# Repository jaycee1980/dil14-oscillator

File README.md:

# dil14-oscillator
A DIL-16 oscillator using a 3.2x2.5mm SMD crystal. Originally I made this for Commodore Amigas, because the 28.6363MHz and 28.37516MHz oscillators are becoming hard to get. Most modern oscillators now are 3.3V types

I found that while they're not common, it IS possible to get crystals of those frequencies in SMD format. For example Mouser have [CTS 403C35D28M37500](https://www.mouser.co.uk/ProductDetail/CTS-Electronic-Components/403C35D28M37500?qs=tjlMjqRIEYSI3TNJCnGYSw%3D%3D) and [ECS 520-286.3-18-33-JGNT](https://www.mouser.co.uk/ProductDetail/ECS/ECS-286.3-18-33-JGN-TR?qs=wd5RIQLrsJjqi%252B%2F66hueEA%3D%3D). These are suitable for use with an Amiga, but they need an oscillator circuit to work. This was easily achievable with the usual Pierce oscillator configuration using logic gates. 

I chose to use a "picogate" type part to keep the size small, the 74LVC2GU04. This is a SOT23-6 part (aka SOT457 o TSOP6) and perfect for the job. 

I've also found that LCSC have suitable crystals in their inventory. They are:

https://www.lcsc.com/product-detail/Crystals_TXC-Corp-7V-28-63636MAHJ-T_C2595058.html

https://www.lcsc.com/product-detail/Crystals_YXC-Crystal-Oscillators-X322528375MSB4SI_C20618000.html

# Whats in this repo? 

In here you can find EAGLE 7.6 board and schematic, Gerber files for manufacture, and BOM + CPL files suitable for use with [JLCPCB](https://jlcpcb.com)

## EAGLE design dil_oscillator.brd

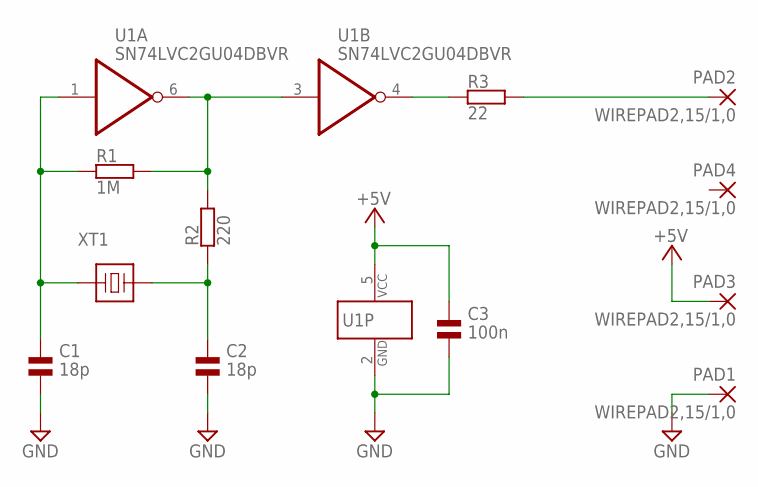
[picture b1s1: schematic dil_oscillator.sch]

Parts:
C1, C2: 18p; 0603
C3: 100n; 0603
PAD1, PAD2, PAD3, PAD4: WIREPAD2,15/1,0; 2,15/1,0
R1: 1M; 0603
R2: 220; 0603
R3: 22; 0603
U1: SN74LVC2GU04DBVR; SOT457
XT1: XTAL_3225; 3225_4PAD

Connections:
+5V: C3.1, PAD3.1, U1.5 (VCC)
GND: C1.2, C2.2, C3.2, PAD1.1, U1.2 (GND)
unnamed: C1.1, R1.1, U1.1 (I), XT1.1
unnamed: R1.2, R2.2, U1.3 (I), U1.6 (O)
unnamed: C2.1, R2.1, XT1.3 (2)
unnamed: R3.1, U1.4 (O)
OUT: PAD2.1, R3.2

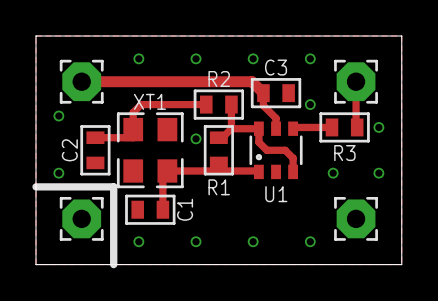
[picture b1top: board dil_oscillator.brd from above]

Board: 2 copper layers, 20.3 x 12.7 mm, 12 parts (0 on the bottom side), 7 nets.

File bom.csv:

Comment,Designator,Footprint,LCSC Part #
18p,C1 C2,0603,C1647
100n,C3,0603,C14663
1M,R1,0603,C22935
220,R2,0603,C22962
22,R3,0603,C23345
SN74LVC2GU04DBVR,U1,SOT-23-6,C139427
28.375MHz,XT1,3225,C20618000

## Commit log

2025-02-22 PDF version of schematic
2025-02-22 updated gitignore
2025-02-23 Added image of the board
